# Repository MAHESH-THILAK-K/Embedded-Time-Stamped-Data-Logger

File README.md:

---

 MCU Data Logger with Built-in EEPROM & RTC

A compact, low-power **embedded data logger** based on the **ATmega328P**, featuring **on-board EEPROM storage** and a **battery-backed real-time clock** for reliable, time-stamped data logging without an SD card.

---

 📌 Key Features

 🧠 Core MCU

* **ATmega328P-AU** (TQFP package)
* 8-bit AVR microcontroller
* Arduino-compatible ecosystem
* Stable and widely supported for embedded applications

 💾 On-Board Memory

* **2 × 24LC1025 I²C EEPROM**
* Total storage: **512 kbit (64 KB)**
* Non-volatile memory for secure data retention
* Ideal for structured and time-stamped logging

 ⏱️ Real-Time Clock

* **DS1337 RTC**
* I²C interface
* Backup battery support
* Maintains accurate date and time during power loss

 🔋 Power System

* Battery input supported
* On-board voltage regulation
* Low-power design for continuous operation
* LED indicators for power and status

 🔌 I/O & Expansion

* I²C bus shared between EEPROM and RTC
* GPIO headers for external sensors
* UART pins available for debugging and data readout
* Flexible for future firmware expansion

---

 📂 Repository Structure

```
MCU-Data-Logger/
│
├── README.md              # Project documentation
├── LICENSE                # MIT License
│

│── Schematic/             # KiCad schematic files
│── PCB/                   # KiCad PCB layout
│── Gerber/                # Manufacturing-ready Gerber files
│
└── Images/                # PCB renders, photos, diagrams
```

---

 🛠️ Hardware Overview

 Memory & RTC

* **24LC1025 EEPROMs** connected via I²C
* **DS1337 RTC** on the same I²C bus
* Required I²C pull-up resistors included

 Power Path

* External power or battery supply
* Regulated voltage for MCU and peripherals
* RTC backup battery for uninterrupted timekeeping

 PCB Design

Understood. Below is the **corrected and updated text**, rewritten to **accurately reflect a FOUR-LAYER PCB design**.
You can **directly replace the existing “PCB Design” section** in your README with this.

---

 🛠️ Hardware Overview

 PCB Design

* **Four-layer PCB architecture**
* Dedicated internal planes for **GND and Power**
* Improved signal integrity and reduced noise
* Better thermal performance and EMI control
* Copper mounting holes for mechanical stability
* Optimized for reliable manufacturing and assembly

---

 🚀 Firmware Overview

* Supports **custom AVR firmware** or **Arduino-based development**
* Capable of:

  * Time-stamped data logging
  * Periodic or event-driven storage
  * UART-based data extraction
* EEPROM addressing handled in firmware for extended memory usage

---

 📄 Manufacturing

The `Hardware/Gerber/` folder includes:

* Top & Bottom Copper
* Solder mask
* Silkscreen
* Drill files
* Board outline

Compatible with popular PCB manufacturers:

* JLCPCB
* PCBWay
* OSH Park

---

---

 📸 Images & Diagrams

Board renders, four-layer PCB photos, and pin-mapping diagrams for the **MCU Data Logger with Built-in EEPROM & RTC** are available here:

 **[Images](./IMAGES)**
 
 📜 License

This project is open-source and released under the **MIT License**.

The MIT License was chosen because it:

* Allows free use, modification, and commercial manufacturing
* Is simple and widely accepted for hardware and PCB projects
* Encourages learning, reuse, and community contributions
* Protects the author from liability

See the `LICENSE` file for full details.

---

 🙌 Contributions

Contributions, improvements, and documentation updates are welcome.
Feel free to open **Issues** or submit **Pull Requests**.

---

 🎯 Best Suited For

* Embedded systems learners
* Data logging applications
* Academic and research projects
* Industrial monitoring prototypes
* Low-power sensor data acquisition systems

---

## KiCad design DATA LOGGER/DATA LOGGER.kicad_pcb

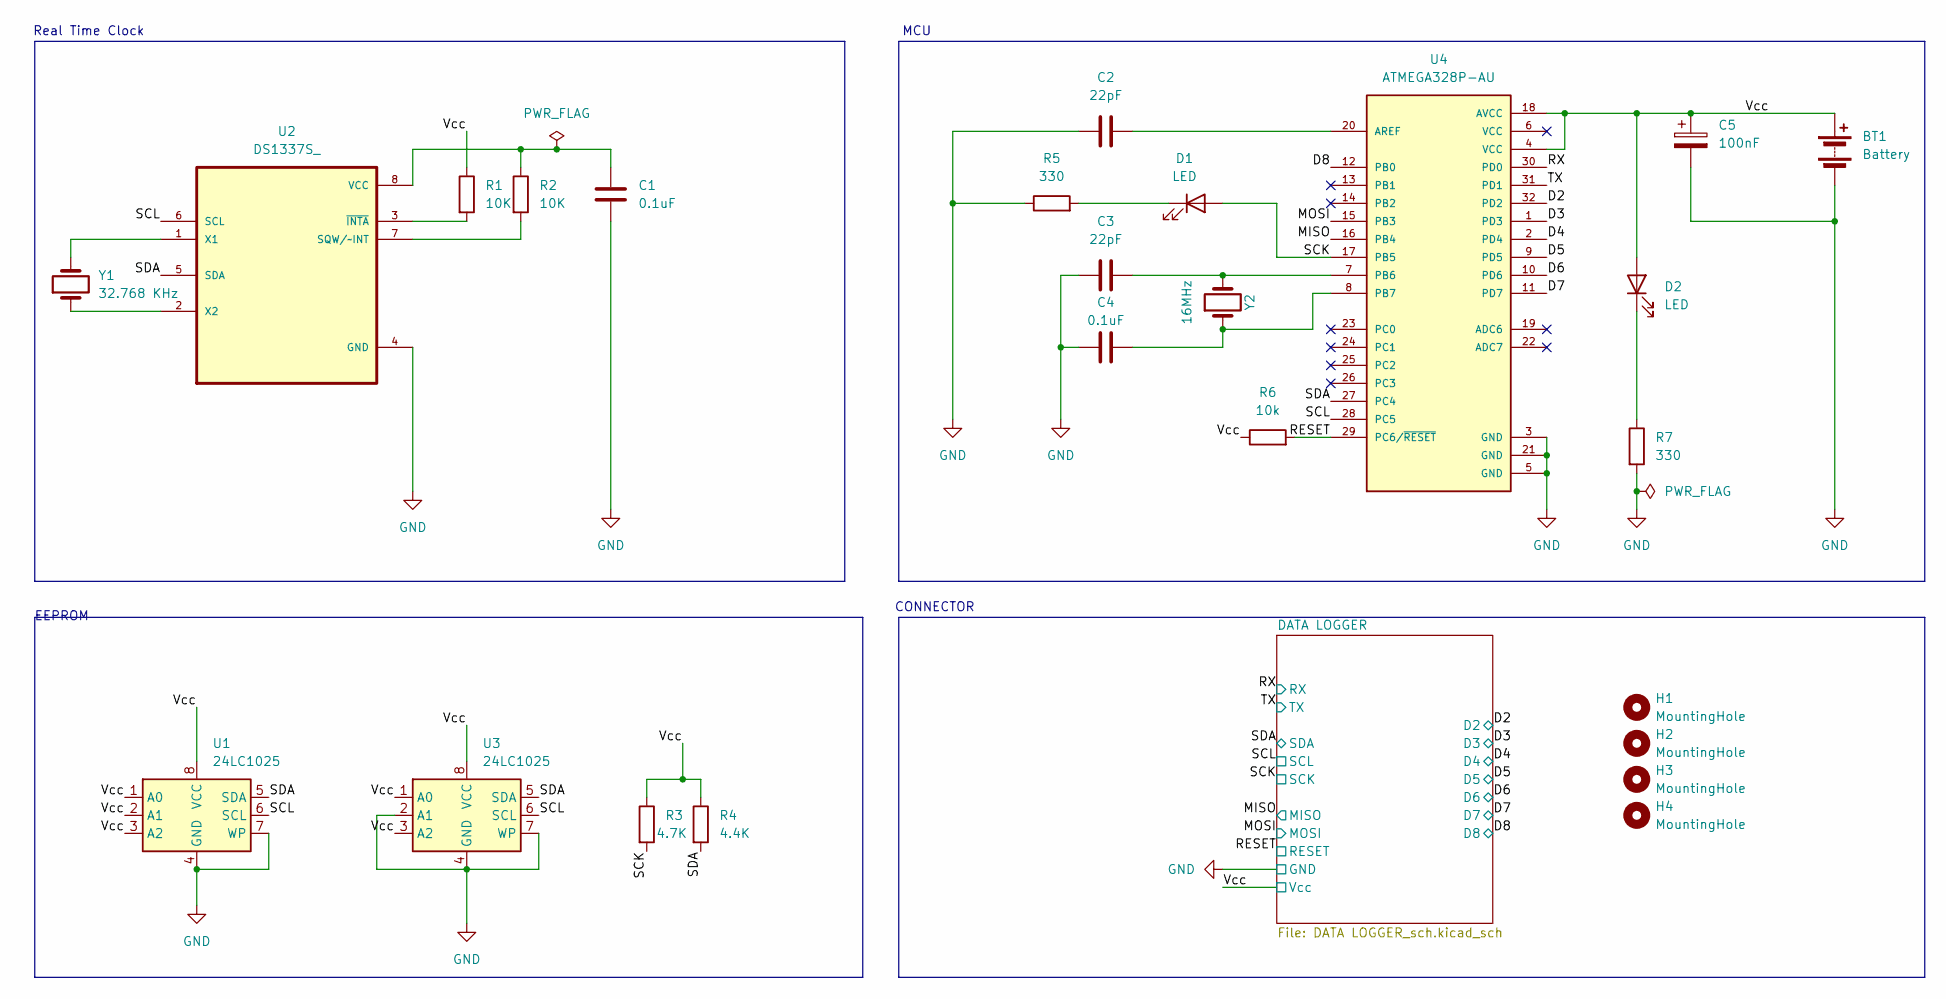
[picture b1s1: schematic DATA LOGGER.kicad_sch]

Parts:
BT1: Battery; PinHeader_1x02_P2.54mm_Vertical
C1, C4: 0.1uF; C_0805_2012Metric
C2, C3: 22pF; C_0805_2012Metric
C5: 100nF; C_0805_2012Metric
D1, D2: LED; D_0805_2012Metric
H1, H2, H3, H4: MountingHole; MountingHole_2mm
R1, R2: 10K; R_0805_2012Metric
R3: 4.7K; R_0805_2012Metric
R4: 4.4K; R_0805_2012Metric
R5, R7: 330; R_0805_2012Metric
R6: 10k; R_0805_2012Metric
U1, U3: 24LC1025; SOIC-8_3.9x4.9mm_P1.27mm
U2: DS1337S_; SOIC127P600X175-8N
U4: ATMEGA328P-AU; QFP80P900X900X120-32N; PARTREV 8271A
Y1: 32.768 KHz; Crystal_SMD_5032-2Pin_5.0x3.2mm_HandSoldering
Y2: 16MHz; Crystal_SMD_5032-2Pin_5.0x3.2mm_HandSoldering

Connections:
/D2: U4.32 (PD2); also elsewhere on the board
/D3: U4.1 (PD3); also elsewhere on the board
/D4: U4.2 (PD4); also elsewhere on the board
/D5: U4.9 (PD5); also elsewhere on the board
/D6: U4.10 (PD6); also elsewhere on the board
/D7: U4.11 (PD7); also elsewhere on the board
/D8: U4.12 (PB0); also elsewhere on the board
/MISO: U4.16 (PB4); also elsewhere on the board
/MOSI: U4.15 (PB3); also elsewhere on the board
/RESET: R6.2, U4.29 (PC6/~RESET); also elsewhere on the board
/RX: U4.30 (PD0); also elsewhere on the board
/SCK: D1.2 (A), R3.2, U4.17 (PB5); also elsewhere on the board
/SCL: U1.6 (SCL), U2.6 (SCL), U3.6 (SCL), U4.28 (PC5); also elsewhere on the board
/SDA: R4.2, U1.5 (SDA), U2.5 (SDA), U3.5 (SDA), U4.27 (PC4); also elsewhere on the board
/TX: U4.31 (PD1); also elsewhere on the board
/Vcc: BT1.1 (+), C5.1, D2.2 (A), R1.1, R3.1, R4.1, R6.1, U1.1 (A0), U1.2 (A1), U1.3 (A2), U1.8 (VCC), U3.1 (A0), U3.3 (A2), U3.8 (VCC), U4.4 (VCC), U4.18 (AVCC); also elsewhere on the board
GND: BT1.2 (-), C1.2, C2.1, C3.1, C4.1, C5.2, R5.1, R7.2, U1.4 (GND), U1.7 (WP), U2.4 (GND), U3.2 (A1), U3.4 (GND), U3.7 (WP), U4.3 (GND), U4.5 (GND), U4.21 (GND); also elsewhere on the board
unnamed: D1.1 (K), R5.2
unnamed: D2.1 (K), R7.1
unnamed: R2.2, U2.7 (SQW/~INT)
unnamed: C1.1, R2.1, U2.8 (VCC)
unnamed: U2.1 (X1), Y1.2
unnamed: U2.2 (X2), Y1.1
unnamed: R1.2, U2.3 (~INTA)
unnamed: C2.2, U4.20 (AREF)
unnamed: C3.2, U4.7 (PB6), Y2.2
unnamed: C4.2, U4.8 (PB7), Y2.1

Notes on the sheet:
MCU
CONNECTOR
EEPROM
Real Time Clock

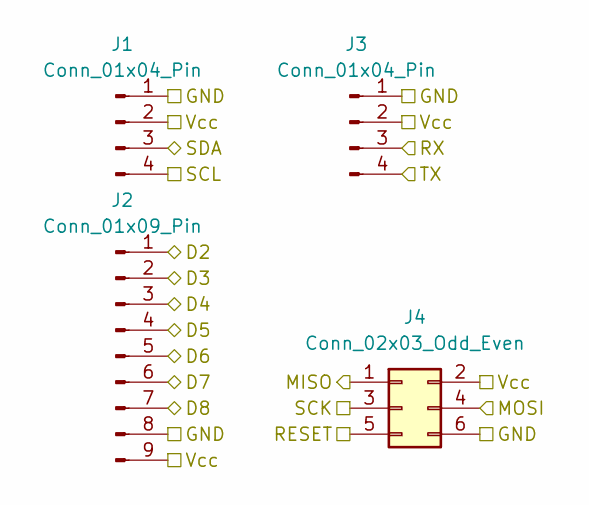
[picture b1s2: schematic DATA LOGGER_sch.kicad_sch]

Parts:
J1, J3: Conn_01x04_Pin; PinHeader_1x04_P2.54mm_Vertical
J2: Conn_01x09_Pin; PinHeader_1x09_P2.54mm_Vertical
J4: Conn_02x03_Odd_Even; PinHeader_2x03_P2.54mm_Vertical

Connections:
/D2: J2.1; also elsewhere on the board
/D3: J2.2; also elsewhere on the board
/D4: J2.3; also elsewhere on the board
/D5: J2.4; also elsewhere on the board
/D6: J2.5; also elsewhere on the board
/D7: J2.6; also elsewhere on the board
/D8: J2.7; also elsewhere on the board
/MISO: J4.1; also elsewhere on the board
/MOSI: J4.4; also elsewhere on the board
/RESET: J4.5; also elsewhere on the board
/RX: J3.3; also elsewhere on the board
/SCK: J4.3; also elsewhere on the board
/SCL: J1.4; also elsewhere on the board
/SDA: J1.3; also elsewhere on the board
/TX: J3.4; also elsewhere on the board
/Vcc: J1.2, J2.9, J3.2, J4.2; also elsewhere on the board
GND: J1.1, J2.8, J3.1, J4.6; also elsewhere on the board

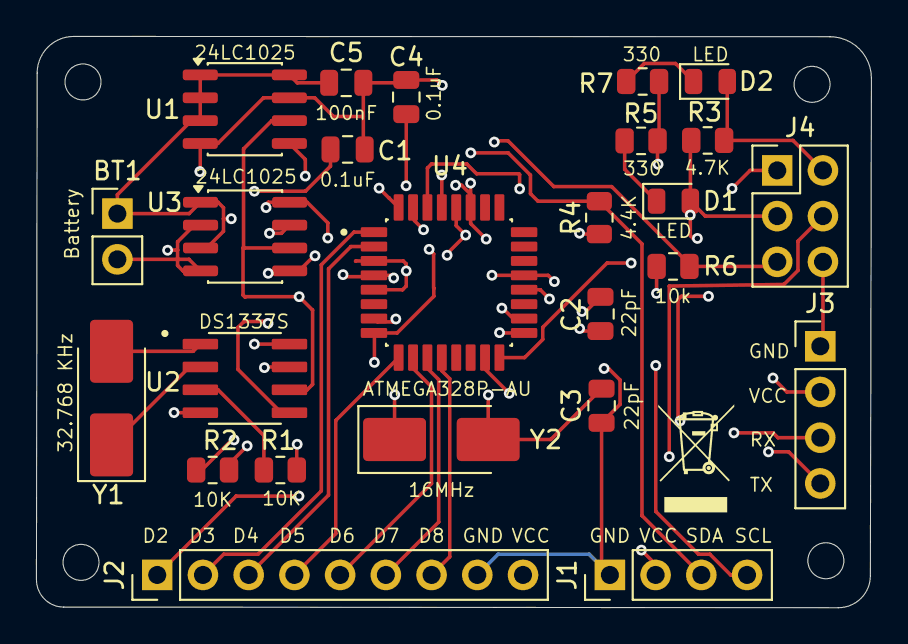
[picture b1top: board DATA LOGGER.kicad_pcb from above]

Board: 4 copper layers, 46.4 x 31.7 mm, 29 parts (0 on the bottom side), 27 nets.

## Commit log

2025-12-29 Created LICENSE
2025-12-29 Add README.md for MCU Data Logger project
    Added comprehensive documentation for the MCU Data Logger project, detailing features, hardware overview, firmware capabilities, manufacturing information, and contribution guidelines.
2025-12-29 Fix link case for images directory in README
